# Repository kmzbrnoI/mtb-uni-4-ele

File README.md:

MTB-UNI v4 PCB
==============

MTB-UNI is an universal IO module featuring 16 digital inputs and 16 digital
outputs. It communicates over [MTBbus](https://mtb.kmz-brno.cz/bus) (RS485).
The module is designed for controlling of the model railroad accessories (such
as turnouts or occupancy detectors), however is could be used generally in
any other application.

This repository contains schematics & PCB layout of MTB-UNI v4 PCB. Firmware
for main MCU ATmega128 is available
[here](https://github.com/kmzbrnoI/mtb-uni-4-fw). More information about
MTB in available [here](https://mtb.kmz-brno.cz/).

## Design

Schematics & PCB are designed in Eagle 9.

## Production

PCB is prepared to be automatically assembled in [JLCPCB](https://jlcpcb.com/).
SMD parts on bottom side should be assembled. Each SMD part has its `LCSC_ITEM`
attribute set.

## Parameters

 * Input voltage: 7–17 V.
   Protection: when > 18 V is applied, input is shorted. Afterwards, current
   is limited by PTC fuse on input to 200 mA. Changed-polarity protection.
 * Max current consumption: 120 mA.
 * Outputs: 16 open collectors. Max current: 200 mA / pin. 500 mA per 8 pins.
   Active-low. Pull-up should be in receiving device.
 * Inputs: 16 active-low digital inputs. Pulled up to +5 V internally.
   Max 5.1 V on input. When bigger voltage applied, input is shorted, current
   is limited to 50 mA by PTC fuse.
 * ULN modules & RS485 drivers are in DIL packages & sockets, so they could
   be easily replaced in case of failure.
 * Screw sockets or connectors could be variably assembled on inputs & outputs
   based on user requirements.

## Piece check

Following checks should be performed to mark each manufactured piece as *QC PASS*.

1. Check module communicates on MTBbus.
2. Check all LEDs are working.
3. Check button is working.
4. Check diagnostic is working.
5. Test module inputs and outputs with [tester.py](https://github.com/kmzbrnoI/mtb-uni-4-fw/blob/master/tester/tester.py).

## Authors

MTB-UNI v4 module was designed by:

 * [Laboratory of railroad control](https://lrkv.pef.mendelu.cz/) Mendel University Brno,
 * [Model Railway Club Brno](https://www.kmz-brno.cz/).

People:

 * Jan Malina (ex. Horáček)
 * Robert Čížek

## License

Content of the repository is provided under [Creative Commons
Attribution-ShareAlike 4.0
License](https://creativecommons.org/licenses/by-sa/4.0/) as openhardware
project. You may download any data, contribute to the project, create PCB
yourself or even sell it yourself.

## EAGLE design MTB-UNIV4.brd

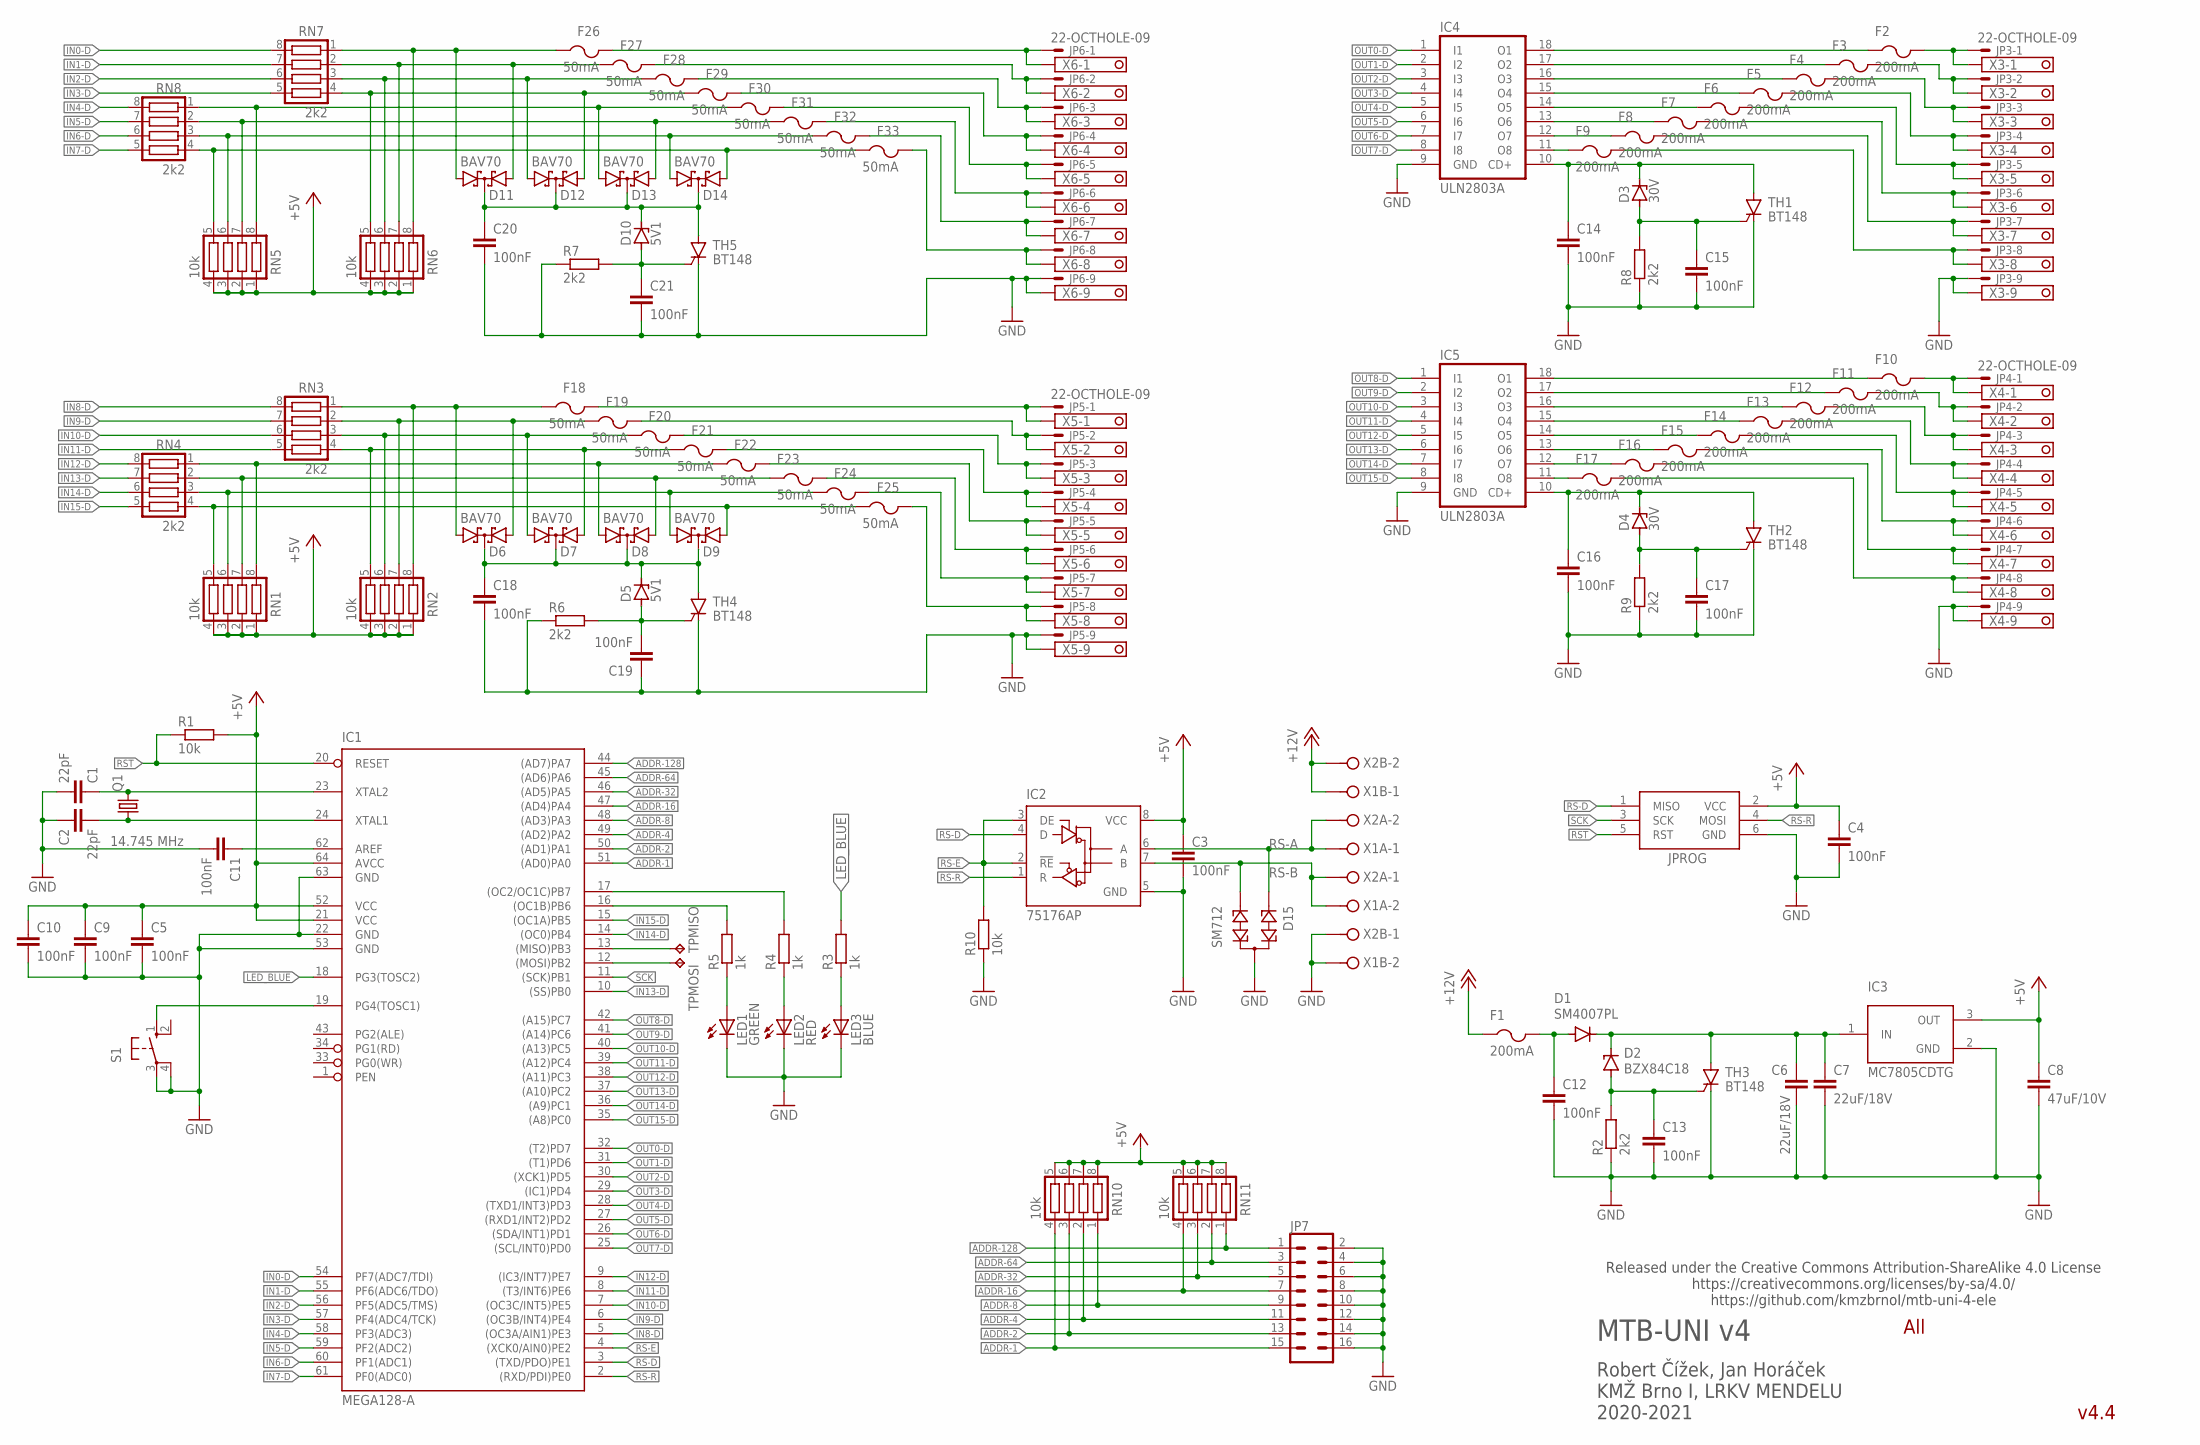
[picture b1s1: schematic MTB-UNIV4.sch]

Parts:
C1, C2: 22pF; C0805; LCSC_PART C1804
C3, C4, C12, C15, C16, C17, C18, C19, C21: 100nF; C0805; LCSC_PART C49678
C5, C10, C11: 100nF; C0805
C6: 22uF/18V; C0805; LCSC_PART C45783
C7: 22uF/18V; C1206
C8: 47uF/10V; C1206; LCSC_PART C96123
C9, C13, C14: 100nF; C0805; LCSC_PART C68978
C20: 100nF; C0805; LCSC_PART C24497
D1: SM4007PL; SOD-123_MINI-SMA; LCSC_PART C64898
D2: BZX84C18; SOT23
D3, D4: 30V; SOT23; LCSC_PART C118586
D5, D10: 5V1; SOT23; LCSC_PART C294621
D6, D7, D8, D9, D11, D12, D13, D14: BAV70; SOT23; LCSC_PART C68978
D15: SM712; SOT23; LCSC_PART C2827658
F1: 200mA; R1206; LCSC_PART C70067
F2, F3, F4, F5, F6, F7, F8, F9, F10, F11, F12, F13, F14, F15, F16, F17: 200mA; R1206S; LCSC_PART C70067
F18, F19, F20, F21, F22, F23, F24, F25, F27, F28, F29, F30, F31, F32, F33: 50mA; R1206S; LCSC_PART C261946
F26: 50mA; R1206S
IC1: MEGA128-A; TQFP64; LCSC_PART C6510
IC2: 75176AP; DIL08
IC3: MC7805CDTG; MC78M05BDTRKG; LCSC_PART C58069
IC4, IC5: ULN2803A; DIL18
JP3, JP4, JP5, JP6: 22-OCTHOLE-09; 7395-09-OCTHOLE
JP7: CONN_08X2; 2X8
JPROG: AVRISP-6; AVRISP
LED1: GREEN; CHIPLED_0805
LED2: RED; CHIPLED_0805
LED3: BLUE; CHIPLED_0805
Q1: 14.745 MHz; HC49UP
R1, R10: 10k; R0805; LCSC_PART C17414
R2, R6, R7, R8, R9: 2k2; R0805; LCSC_PART C17520
R3, R4, R5: 1k; R0805
RN1, RN2, RN5, RN6, RN10, RN11: 10k; CTS742C083; LCSC_PART C29718
RN3, RN4, RN7, RN8: 2k2; CTS742C083; LCSC_PART C12001
S1: 10-XX; B3F-10XX
TH1, TH2, TH4, TH5: BT148; SOT223; LCSC_PART C256433
TH3: BT148; SOT223
TPMISO: TPTP10R; TP10R
TPMOSI: TPTP10R; TP10R
X1A, X1B, X2A, X2B: MVE252-5-V
X3, X4, X5, X6: 1751316

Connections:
+5V: C3.1, C4.1, C5.1, C8.1, C9.1, C10.1, IC1.21 (VCC), IC1.52 (VCC), IC1.64 (AVCC), IC2.8 (VCC), IC3.3 (OUT), JPROG.2 (VCC), R1.2, RN1.1, RN1.2, RN1.3, RN1.4, RN2.1, RN2.2, RN2.3, RN2.4, RN5.1, RN5.2, RN5.3, RN5.4, RN6.1, RN6.2, RN6.3, RN6.4, RN10.5, RN10.6, RN10.7, RN10.8, RN11.5, RN11.6, RN11.7, RN11.8
+12V: F1.1, X1B.1, X2B.2
+12V-IN: C6.1, C7.1, D1.C, D2.3 (C), IC3.1 (IN), TH3.2 (A)
+12V_MIN: C12.1, D1.A, F1.2
ADDR-1: IC1.51 ((AD0)PA0), JP7.15, RN10.4
ADDR-2: IC1.50 ((AD1)PA1), JP7.13, RN10.3
ADDR-4: IC1.49 ((AD2)PA2), JP7.11, RN10.2
ADDR-8: IC1.48 ((AD3)PA3), JP7.9, RN10.1
ADDR-16: IC1.47 ((AD4)PA4), JP7.7, RN11.4
ADDR-32: IC1.46 ((AD5)PA5), JP7.5, RN11.3
ADDR-64: IC1.45 ((AD6)PA6), JP7.3, RN11.2
ADDR-128: IC1.44 ((AD7)PA7), JP7.1, RN11.1
AREF: C11.1, IC1.62 (AREF)
BTN: IC1.19 (PG4(TOSC1)), S1.1 (S)
GND: C1.2, C2.1, C3.2, C4.2, C5.2, C6.2, C7.2, C8.2, C9.2, C10.2, C11.2, C12.2, C13.2, C14.2, C15.2, C16.2, C17.2, C18.2, C19.1, C20.2, C21.2, D15.3, IC1.22 (GND), IC1.53 (GND), IC1.63 (GND), IC2.5 (GND), IC3.2 (GND), IC4.9 (GND), IC5.9 (GND), JP3.9, JP4.9, JP5.9, JP6.9, JP7.2, JP7.4, JP7.6, JP7.8, JP7.10, JP7.12, JP7.14, JP7.16, JPROG.6 (GND), LED1.C, LED2.C, LED3.C, R2.1, R6.1, R7.1, R8.1, R9.1, R10.1, S1.3, S1.4 (P1), TH1.1 (C), TH2.1 (C), TH3.1 (C), TH4.1 (C), TH5.1 (C), X1B.2, X2B.1, X3.9, X4.9, X5.9, X6.9
IN0-D: IC1.54 (PF7(ADC7/TDI)), RN7.8
IN0-R: F26.2, JP6.1, X6.1
IN0-U: D11.1 (A1), F26.1, RN6.8, RN7.1
IN1-D: IC1.55 (PF6(ADC6/TDO)), RN7.7
IN1-R: F27.2, JP6.2, X6.2
IN1-U: D11.2 (A2), F27.1, RN6.7, RN7.2
IN2-D: IC1.56 (PF5(ADC5/TMS)), RN7.6
IN2-R: F28.2, JP6.3, X6.3
IN2-U: D12.1 (A1), F28.1, RN6.6, RN7.3
IN3-D: IC1.57 (PF4(ADC4/TCK)), RN7.5
IN3-R: F29.2, JP6.4, X6.4
IN3-U: D12.2 (A2), F29.1, RN6.5, RN7.4
IN4-D: IC1.58 (PF3(ADC3)), RN8.8
IN4-R: F30.2, JP6.5, X6.5
IN4-U: D13.1 (A1), F30.1, RN5.8, RN8.1
IN5-D: IC1.59 (PF2(ADC2)), RN8.7
IN5-R: F31.2, JP6.6, X6.6
IN5-U: D13.2 (A2), F31.1, RN5.7, RN8.2
IN6-D: IC1.60 (PF1(ADC1)), RN8.6
IN6-R: F32.2, JP6.7, X6.7
IN6-U: D14.1 (A1), F32.1, RN5.6, RN8.3
IN7-D: IC1.61 (PF0(ADC0)), RN8.5
IN7-R: F33.2, JP6.8, X6.8
IN7-U: D14.2 (A2), F33.1, RN5.5, RN8.4
IN8-D: IC1.5 ((OC3A/AIN1)PE3), RN3.8
IN8-R: F18.2, JP5.1, X5.1
IN8-U: D6.1 (A1), F18.1, RN2.8, RN3.1
IN9-D: IC1.6 ((OC3B/INT4)PE4), RN3.7
IN9-R: F19.2, JP5.2, X5.2
IN9-U: D6.2 (A2), F19.1, RN2.7, RN3.2
IN10-D: IC1.7 ((OC3C/INT5)PE5), RN3.6
IN10-R: F20.2, JP5.3, X5.3
IN10-U: D7.1 (A1), F20.1, RN2.6, RN3.3
IN11-D: IC1.8 ((T3/INT6)PE6), RN3.5
IN11-R: F21.2, JP5.4, X5.4
IN11-U: D7.2 (A2), F21.1, RN2.5, RN3.4
IN12-D: IC1.9 ((IC3/INT7)PE7), RN4.8
IN12-R: F22.2, JP5.5, X5.5
IN12-U: D8.1 (A1), F22.1, RN1.8, RN4.1
IN13-D: IC1.10 ((SS)PB0), RN4.7
IN13-R: F23.2, JP5.6, X5.6
IN13-U: D8.2 (A2), F23.1, RN1.7, RN4.2
IN14-D: IC1.14 ((OC0)PB4), RN4.6
IN14-R: F24.2, JP5.7, X5.7
IN14-U: D9.1 (A1), F24.1, RN1.6, RN4.3
IN15-D: IC1.15 ((OC1A)PB5), RN4.5
IN15-R: F25.2, JP5.8, X5.8
IN15-U: D9.2 (A2), F25.1, RN1.5, RN4.4
LED_BLUE: IC1.18 (PG3(TOSC2)), R3.2
LED_GREEN: IC1.16 ((OC1B)PB6), R5.2
LED_RED: IC1.17 ((OC2/OC1C)PB7), R4.2
MISO: IC1.13 ((MISO)PB3), TPMISO.TP
MOSI: IC1.12 ((MOSI)PB2), TPMOSI.TP
unnamed: C16.1, D4.3 (C), IC5.10 (CD+), TH2.2 (A)
unnamed: C14.1, D3.3 (C), IC4.10 (CD+), TH1.2 (A)
unnamed: C15.1, D3.1 (A), R8.2, TH1.3 (G)
unnamed: C17.1, D4.1 (A), R9.2, TH2.3 (G)
unnamed: C13.1, D2.1 (A), R2.2, TH3.3 (G)
unnamed: LED2.A, R4.1
unnamed: LED1.A, R5.1
unnamed: LED3.A, R3.1
unnamed: C18.1, D5.3 (C), D6.3 (CC), D7.3 (CC), D8.3 (CC), D9.3 (CC), TH4.2 (A)
unnamed: C19.2, D5.1 (A), R6.2, TH4.3 (G)
unnamed: C20.1, D10.3 (C), D11.3 (CC), D12.3 (CC), D13.3 (CC), D14.3 (CC), TH5.2 (A)
unnamed: C21.1, D10.1 (A), R7.2, TH5.3 (G)
OUT0-D: IC1.32 ((T2)PD7), IC4.1 (I1)
OUT0-R: F2.2, JP3.1, X3.1
OUT0-U: F2.1, IC4.18 (O1)
OUT1-D: IC1.31 ((T1)PD6), IC4.2 (I2)
OUT1-R: F3.2, JP3.2, X3.2
OUT2-D: IC1.30 ((XCK1)PD5), IC4.3 (I3)
OUT2-R: F4.2, JP3.3, X3.3
OUT2-U: F4.1, IC4.16 (O3)
OUT3-D: IC1.29 ((IC1)PD4), IC4.4 (I4)
OUT3-R: F5.2, JP3.4, X3.4
OUT3-U: F5.1, IC4.15 (O4)
OUT4-D: IC1.28 ((TXD1/INT3)PD3), IC4.5 (I5)
OUT4-R: F6.2, JP3.5, X3.5
OUT4-U: F6.1, IC4.14 (O5)
OUT5-D: IC1.27 ((RXD1/INT2)PD2), IC4.6 (I6)
OUT5-R: F7.2, JP3.6, X3.6
OUT5-U: F7.1, IC4.13 (O6)
OUT6-D: IC1.26 ((SDA/INT1)PD1), IC4.7 (I7)
OUT6-R: F8.2, JP3.7, X3.7
OUT6-U: F8.1, IC4.12 (O7)
OUT7-D: IC1.25 ((SCL/INT0)PD0), IC4.8 (I8)
OUT7-R: F9.2, JP3.8, X3.8
OUT7-U: F9.1, IC4.11 (O8)
OUT8-D: IC1.42 ((A15)PC7), IC5.1 (I1)
OUT8-R: F10.2, JP4.1, X4.1
OUT8-U: F10.1, IC5.18 (O1)
OUT9-D: IC1.41 ((A14)PC6), IC5.2 (I2)
OUT9-R: F11.2, JP4.2, X4.2
OUT9-U: F11.1, IC5.17 (O2)
OUT10-D: IC1.40 ((A13)PC5), IC5.3 (I3)
OUT10-R: F12.2, JP4.3, X4.3
OUT10-U: F12.1, IC5.16 (O3)
OUT11-D: IC1.39 ((A12)PC4), IC5.4 (I4)
OUT11-R: F13.2, JP4.4, X4.4
OUT11-U: F13.1, IC5.15 (O4)
OUT12-D: IC1.38 ((A11)PC3), IC5.5 (I5)
OUT12-R: F14.2, JP4.5, X4.5
OUT12-U: F14.1, IC5.14 (O5)
OUT13-D: IC1.37 ((A10)PC2), IC5.6 (I6)
OUT13-R: F15.2, JP4.6, X4.6
OUT13-U: F15.1, IC5.13 (O6)
OUT14-D: IC1.36 ((A9)PC1), IC5.7 (I7)
OUT14-R: F16.2, JP4.7, X4.7
OUT14-U: F16.1, IC5.12 (O7)
OUT15-D: IC1.35 ((A8)PC0), IC5.8 (I8)
OUT15-R: F17.2, JP4.8, X4.8
OUT15-U: F17.1, IC5.11 (O8)
OUT-1U: F3.1, IC4.17 (O2)
RS-A: D15.1, IC2.6 (A), X1A.1, X2A.2
RS-B: D15.2, IC2.7 (B), X1A.2, X2A.1
RS-D: IC1.3 ((TXD/PDO)PE1), IC2.4 (D), JPROG.1 (MISO)
RS-E: IC1.4 ((XCK0/AIN0)PE2), IC2.2 (!RE), IC2.3 (DE), R10.2
RS-R: IC1.2 ((RXD/PDI)PE0), IC2.1 (R), JPROG.4 (MOSI)
RST: IC1.20 (RESET), JPROG.5 (RST), R1.1
SCK: IC1.11 ((SCK)PB1), JPROG.3 (SCK)
XTAL1: C2.2, IC1.24 (XTAL1), Q1.1
XTAL2: C1.1, IC1.23 (XTAL2), Q1.2

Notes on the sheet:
MTB-UNI v4
Robert Čížek, Jan Horáček KMŽ Brno I, LRKV MENDELU 2020-2021
v4.4
All
Released under the Creative Commons Attribution-ShareAlike 4.0 License https://creativecommons.org/licenses/by-sa/4.0/ https://github.com/kmzbrnoI/mtb-uni-4-ele

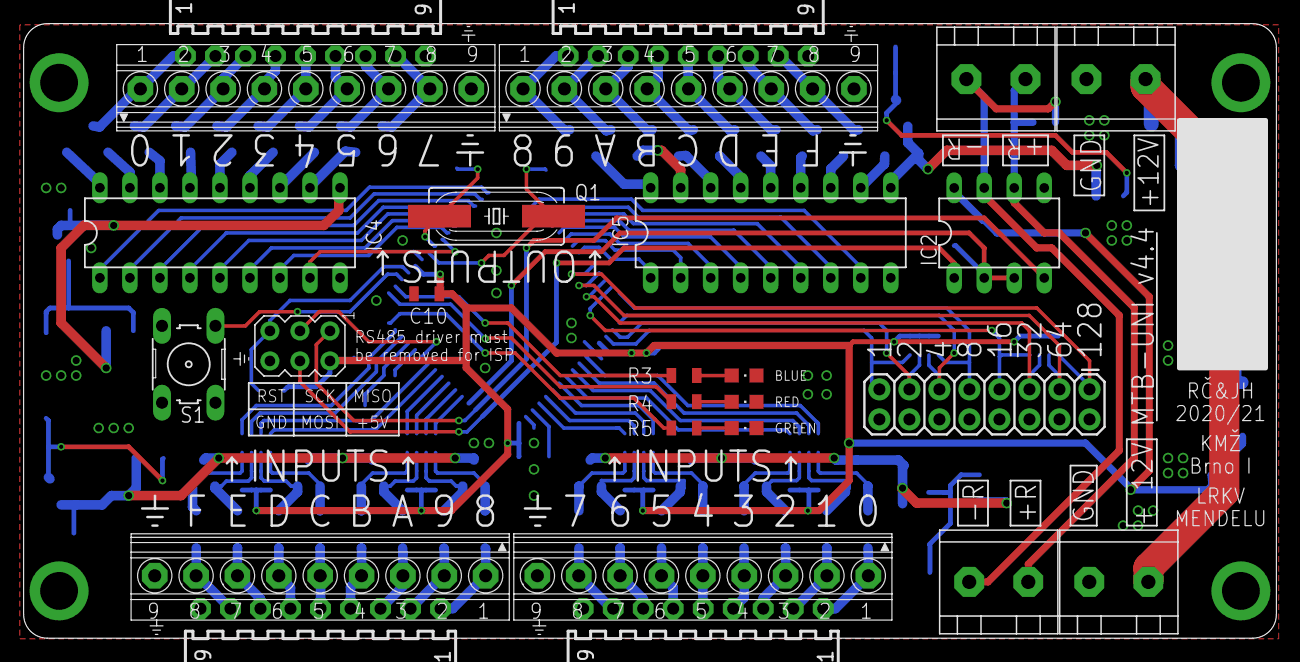
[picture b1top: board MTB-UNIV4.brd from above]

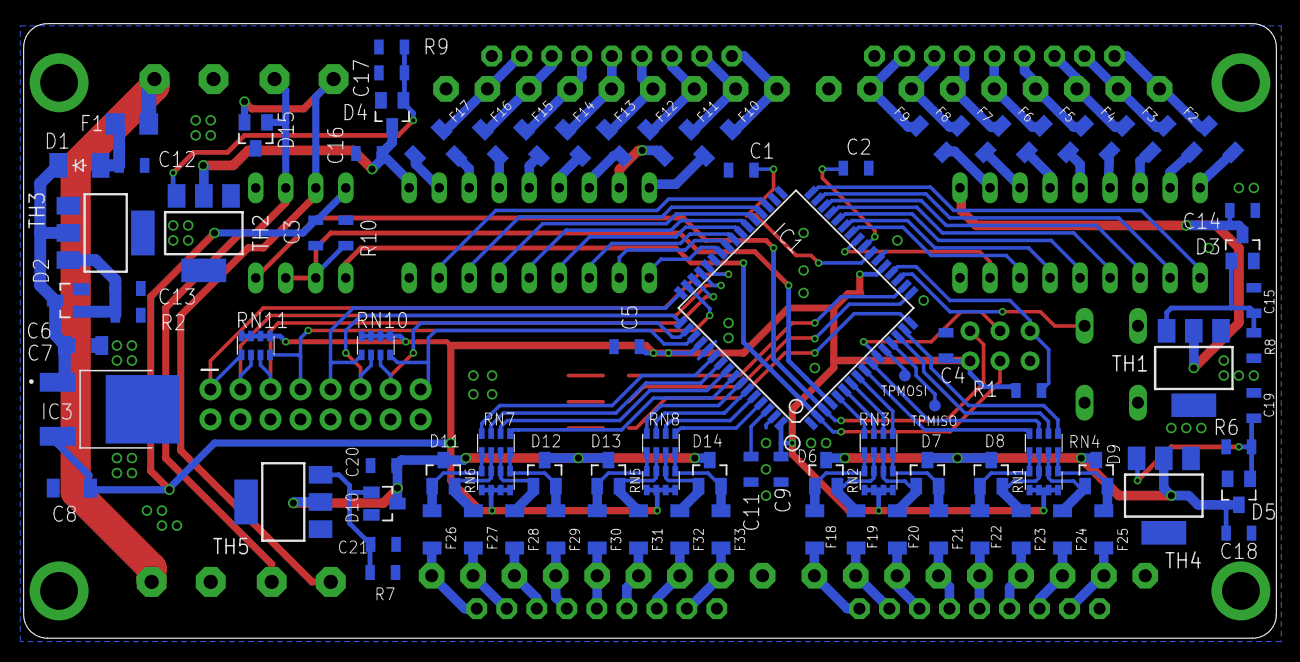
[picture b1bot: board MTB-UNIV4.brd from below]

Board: 2 copper layers, 106.0 x 52.0 mm, 120 parts (94 on the bottom side), 137 nets.

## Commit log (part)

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2020-08-02 Add LICENSE
2020-08-02 prázdný projekt
2020-08-02 přidány ULN2803A a multiplexery pro digitální IO
2020-08-24 Prototyp 1, chybí svorkovnice vstupů a výstupů, selektor adresy a indikační led diody. Možná dodělat ochranu výstupů, ale kdyžtak shoří ULN.
2020-08-24 upravený gitignore, přidány soubory *.b#x a *.s#x
2020-08-26 Use frame A3.
2020-09-06 Vyměněno treset tlačítko za jumper
2020-09-06 vloženy hodnoty k pasívním součástkám
2020-09-06 odstraněn odpor zátěže pro RS-485. dle požadavku v #4
2020-09-06 přidán svodový kondenzátor C27 pro MCU (vývody na více stranách. řešení pro #3
2020-09-06 přejmenovány ULN
2020-09-06 Přidány vstupní části
2020-09-06 Přidány jumpery pro adresaci na sběrnici
2020-10-06 Nahradil jsem spojení COM na ULN Crowbar přepěťovou ochranou. Je to trochu více součástek, ale rozhodně to bude fungovat.
2020-10-06 To stejné jako na vstupech ULN jsem udělal i na vstupu stabilizátoru. Tyristor v Crowbar obvodu proti přepětí.
2020-10-06 Odstraněny kondenzátory na vstupech
2020-10-07 Upraveno po změnách součástek z TME na GME, doplněny LED diody, nahrazeny headry na 9PIN (IO 8+1)
2020-10-07 přidány vodící prvky pro Pick&Place stroje
2020-10-07 Přidán na test molex 3-pin 8x pro jeden výstup.
2020-10-11 Přidány konektory a patice dle požadavků a přidána přepěťová ochrana jako u výstupů
2020-10-11 přidány soubory routingu do ignore listu
2020-10-11 Rozmístěnjy součástky na desku, první kroky routingu. Opraveny drobné nedostatky
2020-11-09 Toto je pokus o naskládání všeho na desku rozměru 106x67mm. Opravdu tam není kam to dát. Nejde o součástky, ale jde o počet spojů. posuvné registry na starých deskách toto vyřešily, ale zde je proces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
2020-11-09 První hotový prototyp MTB nástupce MTB uni s rozměry 106x67mm a roztečí montážních otvorů 100x55mm.
2020-11-10 Do not ground mount holes.
2020-11-11 Fit board to MTB-TTL size.
    Make board smaller.
2020-11-11 TTL-SIZE: everything routed.
2020-11-11 Add some GND vias.
2020-11-11 Remove wire stubs.
2020-11-11 Add net classes.
2020-11-11 Add fiducials.
2020-11-11 Schematics: add info text.
2020-11-11 Inputs: IN-PULL-PROT-CPU.
2020-11-13 Add 12V clearence 1 mm.
2020-11-18 Add 75176 EN pulldown (for CPU programming etc)
2020-11-18 Add labels.
2020-11-18 Place values.
2020-11-18 Add info text & place for address & CPU version.
2020-11-18 Add values.
2020-11-18 Move resistors for better manufacturing.
2020-11-18 Minor wire move.
2020-11-18 Add fiducials to bottom.
2020-11-18 Remove reset.
    Reset could be done via programming connector.
2020-11-18 Add a button.
2020-11-18 Move names.
2020-11-19 Remove fiducials.
2020-11-19 Unify drill size.
2020-11-19 Add Schottky diode value.
2020-11-20 Add crystal frequency.
2020-11-20 Add LEDs color.
2020-11-20 Add diode value.
2020-11-20 Add assembly variants PFH / SVORK.
2020-11-20 Add IO descriptions.
2020-11-20 Add pinhead bits description.
2020-11-20 Remove unused layers.
2020-11-21 Make edges round.
2020-11-21 Add borders around silkscreen descriptions.
2020-11-27 Do not version eagle.epf.
2020-11-27 Add info to READM
2020-11-27 Use BAT54C diodes.
2020-12-03 Use diacritics.
2020-12-04 Use vector font in schematics, use diacritics.
2020-12-14 Use ceramic capacitors only.
    Reduce parts count.
2020-12-14 Use diode available at JLCPCB as basic part.
2021-01-27 Reposition silksreen labels.
2021-01-28 Use proper sockets (MVE252-5-V).
2021-01-28 Fix output Zener diodes values.
2021-02-04 Add LCSC numbers.
2021-02-05 Make corners more round.
2021-02-06 Change licence to Creative Commons as this is HW.
2021-02-06 Add more info to README.
2021-02-11 Fix LCSC.
2021-02-11 Use resistor network.
2021-02-12 Change parts for 0805, add blue LED.
2021-02-12 Use SMD crystal to add space for IO numbers.
2021-02-12 Add silkscreen texts.
2021-02-12 Renumber parts.
2021-02-12 Fix DRC errors.
2021-02-12 Fix LCSCs.
2021-02-12 Reposition silkscreen parts names.
2021-02-12 Fix wrong LCSCs.
2021-02-23 Add programming connector description.
2021-02-23 Revert zener diodes on inputs to 5V1.
    5V1 diodes open tyrristor at ~4V8.
2021-03-17 Add right MCU pins to programming connector.
2021-03-17 Fix LCSC part of resonator's capacitors.
2021-03-24 Name almost all wires properly.
2021-03-26 Use 0805 LEDs.
2021-03-26 Reposition place.
2021-10-15 Add test pads for MOSI & MISO.
2021-11-04 Add AREF 100nF capacitor.
2021-11-06 Use 75176 part from standard library.
2021-11-06 RS485: add ESD protection.
2021-11-06 Fix silkscreen.
2021-11-06 Fix silkscreen, add BT148 LCSC part numbers.
2021-11-25 Fix bad LCSC parts.
2021-11-26 Fix LEDs description on silkscreen.
2021-11-26 Fix switched blue LED too.

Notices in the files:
parts and their libraries:
SparkFun-Connectors: Licensing: Creative Commons ShareAlike 4.0 International - https://creativecommons.org/licenses/by-sa/4.0
